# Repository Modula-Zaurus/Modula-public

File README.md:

# Modula

Modulaは、共同開発したMeKaBuの後継となるモジュール式キーボードです。[MeKaBuのモジュール](https://github.com/Modulable-Keyboard-Developer/public-data)を再利用する構想を引き継ぎ、Modula向けにも新しいモジュールを開発しています。

このリポジトリには、**左右の本体基板のKiCad設計・製造用出力と、筐体のSTEP・3MF**を収録しています。ファームウェアは同じGitHub組織の [zmk-config-Modula](https://github.com/Modula-Zaurus/zmk-config-Modula) を参照してください。設計の閲覧や改良の出発点として利用できます。ただし、本リポジトリには外部CADライブラリ、全体の部品表、組立手順が揃っておらず、この一式だけで完成品を再現できる状態ではありません。

## 収録範囲

| 対象 | 設計・交換データ | 製造用出力・関連資料 | 確認状況 |
| --- | --- | --- | --- |
| 左本体基板 | [KiCadプロジェクト](electrical/Shield_L/Shield_L.kicad_pro)、[回路図](electrical/Shield_L/Shield_L.kicad_sch)、[基板](electrical/Shield_L/Shield_L.kicad_pcb)、[STEP](electrical/Shield_L/Shield_L_Modula.step) | [Gerber ZIP](electrical/Shield_L/jlcpcb/production_files/GERBER-Shield_L.zip)、[実装用BOM](electrical/Shield_L/jlcpcb/production_files/BOM-Shield_L.csv)、[CPL](electrical/Shield_L/jlcpcb/production_files/CPL-Shield_L.csv) | 静的検証で警告あり。実機動作記録なし |
| 右本体基板 | [KiCadプロジェクト](electrical/Shield_R/Shield_R.kicad_pro)、[回路図](electrical/Shield_R/Shield_R.kicad_sch)、[基板](electrical/Shield_R/Shield_R.kicad_pcb)、[STEP](electrical/Shield_R/Shield_R_Modula.step) | [Gerber ZIP](electrical/Shield_R/jlcpcb/production_files/GERBER-Shield_R.zip)、[実装用BOM](electrical/Shield_R/jlcpcb/production_files/BOM-Shield_R.csv)、[CPL](electrical/Shield_R/jlcpcb/production_files/CPL-Shield_R.csv) | 静的検証で警告あり。実機動作記録なし |
| 左筐体 | [Left](mechanical/Left)：トッププレートv2_3、ボトムケースv2_7 | STEP | 元CADの履歴・拘束は未収録 |
| 右筐体 | [Right](mechanical/Right)：トッププレートv2_4、ボトムケースv2_8 | STEP | 元CADの履歴・拘束は未収録 |
| 共通部品 | [Common](mechanical/Common)：ノブ、スペーサー、ブロック、左右マイコンカバー、電源・リセット操作部 | STEP | ファイル名で数量指定のあるスペーサー・ブロックは左右合計各8個。実物との照合は未実施 |
| FDM印刷用プロジェクト | [Modula_FDM.3mf](mechanical/Modula_FDM.3mf) | Bambu Studioの設定・メッシュ・プレビューを内包 | 実際のプリンター・材料に合わせた確認が必要 |

`electrical/` は電気設計、`mechanical/` は機械設計の交換・印刷データです。バックアップ・旧回路図は公開対象に含めません。

## 拡張モジュールとMeKaBu互換性

[写真付きの新規開発モジュール紹介](https://buymeacoffee.com/bparound30s/modula5)では、次の5点を紹介しています（名称は開発者提供情報に基づきます）。

| モジュール | このリポジトリ内の対応設計 |
| --- | --- |
| 19mm低背トラックボール | 設計データは現在非公開 |
| マウスユニット（左右・中クリック、スクロールエンコーダー） | 同上 |
| 11mmステンレストラックボール＋エンコーダー | 同上 |
| センタープッシュ付きLR回路付きエンコーダー | 同上 |
| LED透過光付きアルチザンキーキャップ用モジュール | 同上 |

これらの拡張モジュールは意図的に公開対象から外しています。今後の公開は、[Buy Me a Coffee](#開発を支援する)での支援状況と、開発者の意欲・作業状況に応じて判断します。支援は公開や公開時期を保証するものではありません。

MeKaBuとの互換性については、対象モジュールの版、コネクターの向き・ピン配置、電源電圧、機械寸法、対応ファームウェアの組合せを示す検証表が未収録です。全モジュールの互換性や動作を保証するものではありません。

## 設計を開く・製造を準備する

1. 左右それぞれの `.kicad_pro` をKiCadで開きます。収録回路図はKiCad 9.0形式、既存Gerberは9.0.7で生成されています。
2. カスタムライブラリは本リポジトリに未同梱です。開発者のComponentsフォルダーには主要フットプリント5種が存在しますが、左右回路図の `mcu:xiao-ble`・`switch:SKRHA`、PCBの `kbd_Hole:m2_Screw_Hole` は外部ライブラリ参照が未解決です。これらの形状・シンボルは設計ファイル内に保持されています。ライブラリからの更新には参照先の復元が必要です。スライドスイッチの標準3Dモデル参照1種も未解決です。
3. ERC・DRCと回路図／基板の整合性を確認します。2026-11-12のKiCad 9.0.7による検証では、DRC警告は左64件・右7件、回路図との整合性警告は左80件・右30件、ERC警告は左右各6件でした。左には基板端クリアランス警告8件を含みます。設計意図を確認してから修正し、製造データを同じ版から出し直してください。
4. Gerberとドリルをビューアーで確認し、BOM・CPLと部品面・原点・回転を照合します。収録Gerber ZIPと展開済み出力は一致していますが、現在のPCBとの版の一致は未確認です。Gerberの日付は左右とも2026-05-02です。
5. **収録BOMは各側1N4148ダイオード40個の実装用リストです。** MCU、スイッチ、ソケット、コネクター、電源、ねじなどを含む完成品の調達表ではありません。全体BOMの確定後に発注してください。
6. 筐体はSTEP対応CADで閲覧・編集するか、3MFをBambu Studioで開き、配置と印刷条件を確認します。3MFの生成アプリ記録はBambuStudio-02.07.01.62です。基板との干渉、ねじ、材料収縮、印刷方向の実機検証は未実施です。

2026-11-12に現行左右PCBからGerber各7層とPTH／NPTHドリルを正常に出力できることを確認しました。外部ライブラリの不足自体は裸基板の発注を妨げません。ただし、出力成功は製造品質・動作の保証ではなく、警告・製造条件・採用版の確認が必要です。検証出力で既存の製造データを置き換えてはいません。

組立順、配線、電源の接続条件、締結部品、完成検査の手順は本リポジトリに未収録です。

## ファームウェア

ファームウェアは [Modula-Zaurus/zmk-config-Modula](https://github.com/Modula-Zaurus/zmk-config-Modula) で別管理しています。利用方法・ビルド設定・配布状況・ライセンスは、リンク先の案内を確認してください。本リポジトリにはファームウェアを同梱しません。製作する基板・モジュール構成と対応版を照合して使用してください。

## ToDo（未解決・未検証事項）

本文で示した未解決・未検証事項と不足資料を整理しています。

### CAD・基板・製造データ

- [ ] 再現に必要なカスタムライブラリを同梱し、別の環境でも参照できる設定を整える。
- [ ] `mcu:xiao-ble`、`switch:SKRHA`、`kbd_Hole:m2_Screw_Hole` のライブラリ参照を復元し、既存のピン番号・形状と照合する。
- [ ] スライドスイッチの標準3Dモデル参照を解決する。
- [ ] 左右基板のERC・DRC・回路図との整合性警告を確認し、修正する項目と設計意図に基づいて許容する項目を記録する。特に左基板の端部クリアランス警告8件を確認する。
- [ ] 製造に使用するPCB版を確定し、収録Gerberとの版の一致を確認する。不一致の場合は同じ版から製造データを再生成する。
- [ ] Gerber・ドリルの表示、発注先の製造条件、BOM・CPLの部品面・原点・回転を照合する。

### 部品・筐体・組立

- [ ] MCU、スイッチ、ソケット、コネクター、電源、ねじなどを含む全体BOMを作成する。
- [ ] 共通部品の形状・数量を実物と照合する（スペーサー・ブロックはファイル名上、左右合計各8個）。
- [ ] 使用するプリンター・材料に合わせて3MFの配置・印刷条件を確認し、基板との干渉、ねじの適合、材料収縮、印刷方向を実機で検証する。
- [ ] 筐体の編集履歴・拘束を含む元CADについて、公開する形式と範囲を決め、公開対象を追加する。
- [ ] 組立順、配線、電源の接続条件、締結部品、完成検査の手順を整備する。

### 動作・互換性

- [ ] 左右本体基板の実機動作を確認し、使用した基板版・部品構成・結果を記録する。
- [ ] 基板・モジュール構成と、別管理のファームウェアの対応版を照合して記録する。
- [ ] MeKaBuモジュールの版、コネクターの向き・ピン配置、電源電圧、機械寸法、対応ファームウェアの組合せを確認し、互換性検証表を作成する。

## ライセンスと出典

自作ハードウェア設計には、既存の [CERN-OHL-W v2（LICENCE）](LICENCE)を維持します。対象は `electrical/` と `mechanical/` の自作設計およびその出力です。権利・出典確認は、所有者による個別の確認と記録の保管に基づき完了しています。第三者素材の既存条件・表示は維持します。第三者素材、ファームウェア、文書・画像に一律に再許諾する宣言ではありません。

第三者もライセンス条件に従って製造・販売できます。製品に対応するComplete Sourceまたはその入手先を購入者へ案内し、改変した対象設計のライセンス・変更表示などの条件を守ってください。作者への支援は販売許可の対価ではありません。販売者による製造・検査・購入者対応と、元の設計者の活動を区別し、作者公認・保証付きと誤認させない表示にしてください。詳細な条件はライセンス本文を参照してください。

## 開発を支援する

[BPのBuy Me a Coffeeで開発を支援する](https://buymeacoffee.com/bparound30s)

支援は開発活動への任意の応援です。部品購入、基板・筐体・機構の試作、動作検証、公開資料の整備に役立てます。完成品の購入・予約や、個別技術サポートの提供を伴うものではありません。

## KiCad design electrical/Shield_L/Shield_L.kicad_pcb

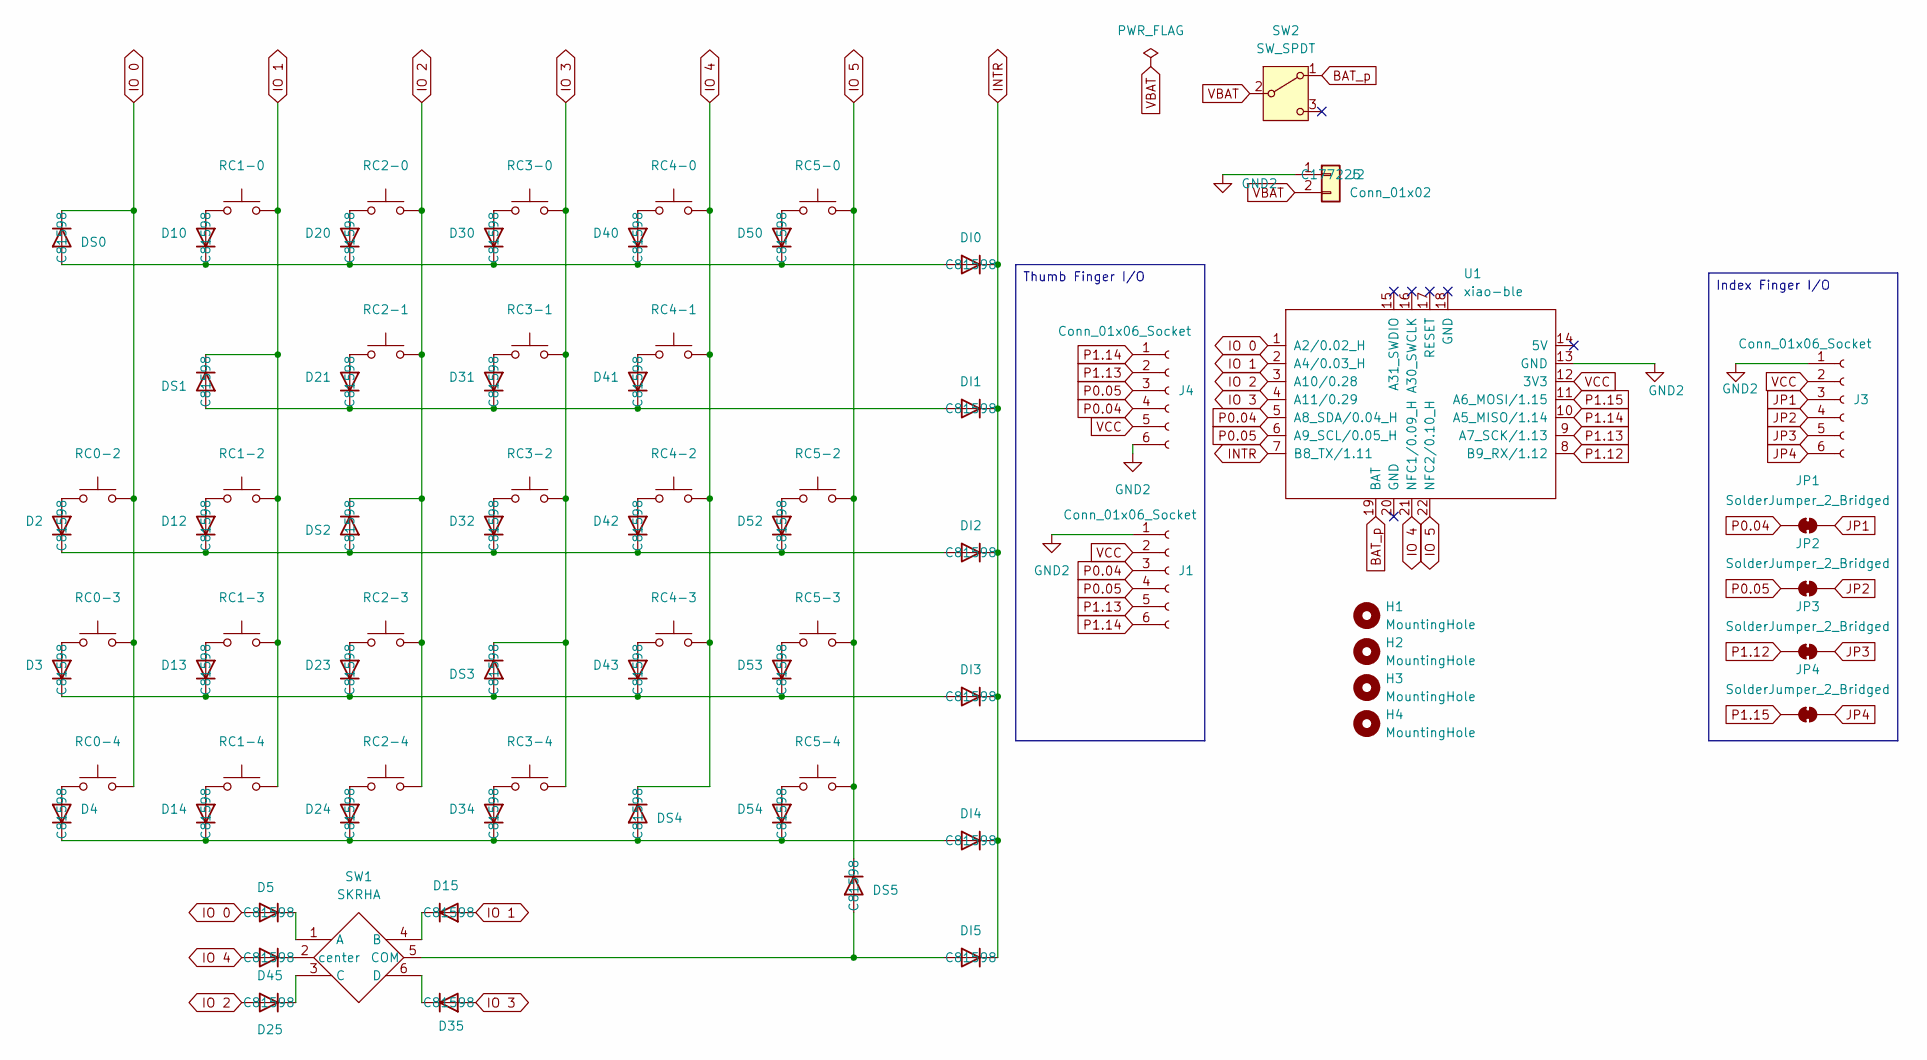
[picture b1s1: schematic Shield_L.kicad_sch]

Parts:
D2, D3, D4, D5, D10, D12, D13, D14, D15, D20, D21, D23, D24, D25, D30, D31, D32, D34, D35, D40, D41, D42, D43, D45, D50, D52, D53, D54: 1N4148; SOD123_DIO; LCSC C81598
DI0, DI1, DI2, DI3, DI4, DI5: 1N4148; SOD123_DIO; LCSC C81598
DS0, DS1, DS2, DS3, DS4, DS5: 1N4148; SOD123_DIO; LCSC C81598
H1, H2, H3, H4: MountingHole; m2_Screw_Hole
J1, J3: Conn_01x06_Socket; PinHeader_1x06_P2.54mm_Vertical
J2: Conn_01x02; Molex_PicoBlade_53261-0271_1x02-1MP_P1.25mm_Horizontal; LCSC C177225
J4: Conn_01x06_Socket; Hirose_FH12-6S-0.5SH_1x06-1MP_P0.50mm_Horizontal; LCSC C202118
JP1, JP2, JP3, JP4: SolderJumper_2_Bridged; SolderJumper-2_P1.3mm_Open_RoundedPad1.0x1.5mm
RC0-2, RC0-3, RC0-4, RC1-0, RC1-2, RC1-3, RC1-4, RC2-0, RC2-1, RC2-3, RC2-4, RC3-0, RC3-1, RC3-2, RC3-4, RC4-0, RC4-1, RC4-2, RC4-3, RC5-0, RC5-2, RC5-3, RC5-4: SW_Push; Choc_v2_Hotswap_1u_narrow
SW1: SKRHA; SKRHA-boss
SW2: SW_SPDT; SW_Slide-03_Wuerth-WS-SLTV_10x2.5x6.4_P2.54mm
U1: xiao-ble; xiao-ble-smd-cutout

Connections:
BAT_p: SW2.1 (A), U1.19 (BAT)
GND2: J1.1, J2.1, J3.1, J4.6, U1.13 (GND)
INTR: DI0.1 (K), DI1.1 (K), DI2.1 (K), DI3.1 (K), DI4.1 (K), DI5.1 (K), U1.7 (B8_TX/1.11)
IO 0: D5.2 (A), DS0.1 (K), RC0-2.1, RC0-3.1, RC0-4.1, U1.1 (A2/0.02_H)
IO 1: D15.2 (A), DS1.1 (K), RC1-0.1, RC1-2.1, RC1-3.1, RC1-4.1, U1.2 (A4/0.03_H)
IO 2: D25.2 (A), DS2.1 (K), RC2-0.1, RC2-1.1, RC2-3.1, RC2-4.1, U1.3 (A10/0.28)
IO 3: D35.2 (A), DS3.1 (K), RC3-0.1, RC3-1.1, RC3-2.1, RC3-4.1, U1.4 (A11/0.29)
IO 4: D45.2 (A), DS4.1 (K), RC4-0.1, RC4-1.1, RC4-2.1, RC4-3.1, U1.21 (NFC1/0.09_H)
IO 5: DS5.1 (K), RC5-0.1, RC5-2.1, RC5-3.1, RC5-4.1, U1.22 (NFC2/0.10_H)
JP1: J3.3, JP1.2 (B)
JP2: J3.4, JP2.2 (B)
JP3: J3.5, JP3.2 (B)
JP4: J3.6, JP4.2 (B)
unnamed: D2.2 (A), RC0-2.2
unnamed: D3.2 (A), RC0-3.2
unnamed: D4.2 (A), RC0-4.2
unnamed: D5.1 (K), SW1.1 (A)
unnamed: D10.2 (A), RC1-0.2
unnamed: D10.1 (K), D20.1 (K), D30.1 (K), D40.1 (K), D50.1 (K), DI0.2 (A), DS0.2 (A)
unnamed: D12.2 (A), RC1-2.2
unnamed: D2.1 (K), D12.1 (K), D32.1 (K), D42.1 (K), D52.1 (K), DI2.2 (A), DS2.2 (A)
unnamed: D13.2 (A), RC1-3.2
unnamed: D3.1 (K), D13.1 (K), D23.1 (K), D43.1 (K), D53.1 (K), DI3.2 (A), DS3.2 (A)
unnamed: D14.2 (A), RC1-4.2
unnamed: D4.1 (K), D14.1 (K), D24.1 (K), D34.1 (K), D54.1 (K), DI4.2 (A), DS4.2 (A)
unnamed: D15.1 (K), SW1.4 (B)
unnamed: D20.2 (A), RC2-0.2
unnamed: D21.2 (A), RC2-1.2
unnamed: D21.1 (K), D31.1 (K), D41.1 (K), DI1.2 (A), DS1.2 (A)
unnamed: D23.2 (A), RC2-3.2
unnamed: D24.2 (A), RC2-4.2
unnamed: D25.1 (K), SW1.3 (C)
unnamed: D30.2 (A), RC3-0.2
unnamed: D31.2 (A), RC3-1.2
unnamed: D32.2 (A), RC3-2.2
unnamed: D34.2 (A), RC3-4.2
unnamed: D35.1 (K), SW1.6 (D)
unnamed: D40.2 (A), RC4-0.2
unnamed: D41.2 (A), RC4-1.2
unnamed: D42.2 (A), RC4-2.2
unnamed: D43.2 (A), RC4-3.2
unnamed: D45.1 (K), SW1.2 (center)
unnamed: D50.2 (A), RC5-0.2
unnamed: D52.2 (A), RC5-2.2
unnamed: D53.2 (A), RC5-3.2
unnamed: D54.2 (A), RC5-4.2
unnamed: DI5.2 (A), DS5.2 (A), SW1.5 (COM)
P0.04: J1.3, J4.4, JP1.1 (A), U1.5 (A8_SDA/0.04_H)
P0.05: J1.4, J4.3, JP2.1 (A), U1.6 (A9_SCL/0.05_H)
P1.12: JP3.1 (A), U1.8 (B9_RX/1.12)
P1.13: J1.5, J4.2, U1.9 (A7_SCK/1.13)
P1.14: J1.6, J4.1, U1.10 (A5_MISO/1.14)
P1.15: JP4.1 (A), U1.11 (A6_MOSI/1.15)
VBAT: J2.2, SW2.2 (B)
VCC: J1.2, J3.2, J4.5, U1.12 (3V3)

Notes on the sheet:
Index Finger I/O
Thumb Finger I/O

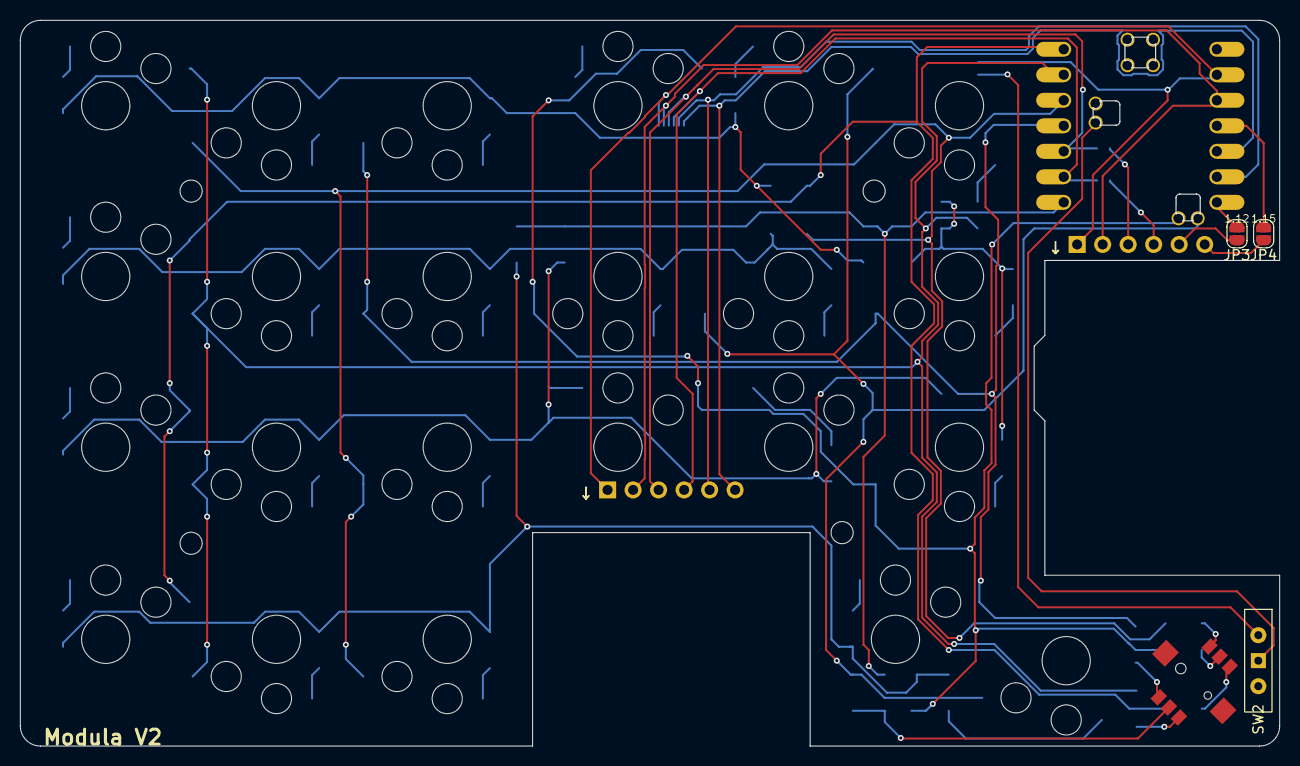
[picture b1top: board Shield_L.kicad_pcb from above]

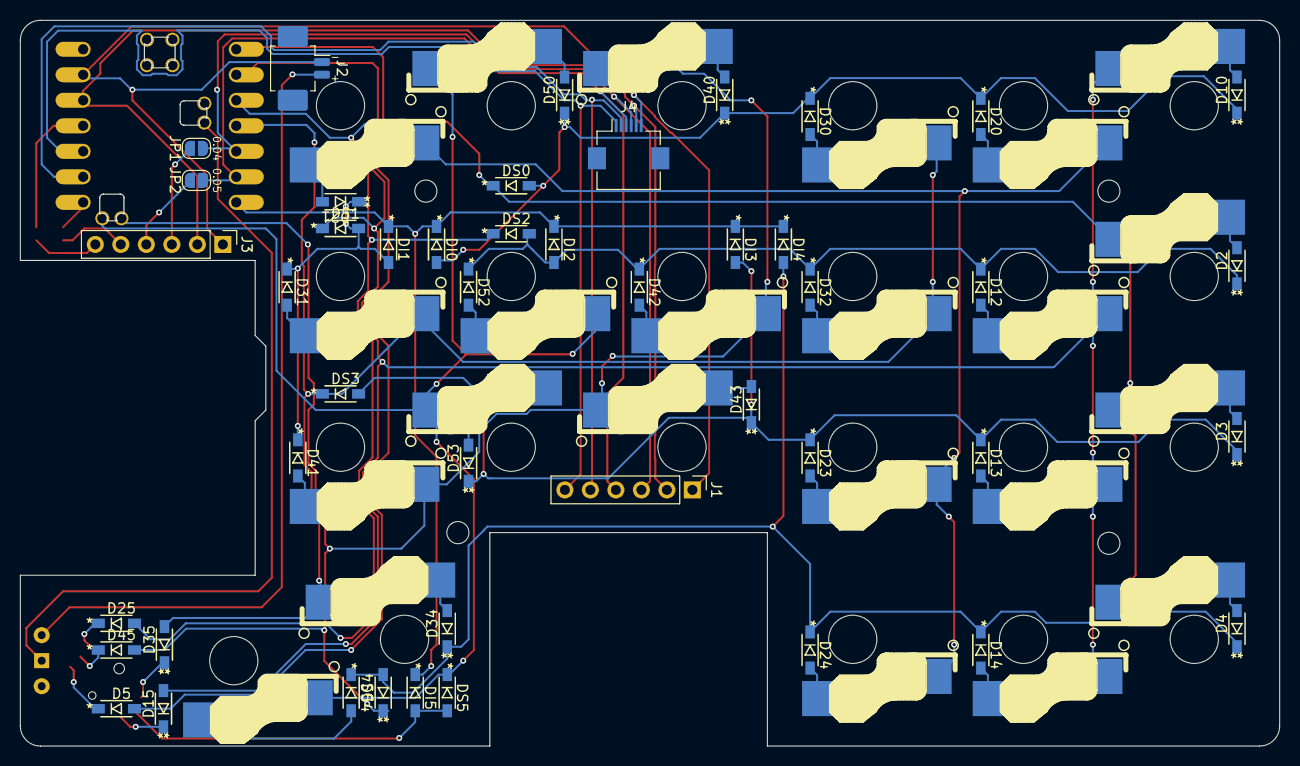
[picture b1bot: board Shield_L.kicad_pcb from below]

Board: 2 copper layers, 125.4 x 72.2 mm, 78 parts (46 on the bottom side), 55 nets.
